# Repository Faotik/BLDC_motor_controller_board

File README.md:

# BLDC Motor Controller Board

A three-phase brushless DC (BLDC) motor controller built around an **STM32F405** microcontroller and a **DRV8305** gate driver. Designed in KiCad for a 12 V supply and 4 A motor current, with a 2x safety margin (8 A) in the power stage.

## Features

- **MCU:** STM32F405RGT6 with a 25 MHz crystal and SWD programming header
- **Motor control:** TIM1 complementary PWM outputs (CH1-3 and CH1N-3N), driver control over SPI, `EN_GATE`, `nFAULT` and `PWRGD` lines
- **Sensing:** shunt-based current sensing (4-wire Kelvin connections), phase voltage sensing (`VSEN_A/B/C`) and a Hall sensor connector
- **Power stage:** three half-bridges with wide power tracks and polygons for high current
- **Power supply:** 12 V input with polyfuse and TVS protection, LM2576 buck converter to 5 V, LM3940 LDO to 3.3 V
- **Wireless:** Bluetooth module

## Schematics

**MCU**

**Power supply**

## Repository layout

| Path | Contents |
|------|----------|
| `project.kicad_pro`, `project.kicad_sch`, `project.kicad_pcb` | KiCad project, top-level schematic and PCB |
| `STM32F405RGT`, `mcu`, `motor_driver`, `power_circuit`, `power_switches`, `bluetooth_module` (`.kicad_sch`) | Schematic sheets |
| `cubemx/` | STM32CubeMX pin and peripheral configuration |
| `Fabrication_files/` | Gerbers and drill files |
| `components/MyComponents.pretty` | Custom footprints |
| `project.csv`, `project-all-pos.csv` | BOM and component placement |

## Opening the project

Open `project.kicad_pro` in KiCad 10 or later.

## Status

Hardware design: schematics and PCB layout.

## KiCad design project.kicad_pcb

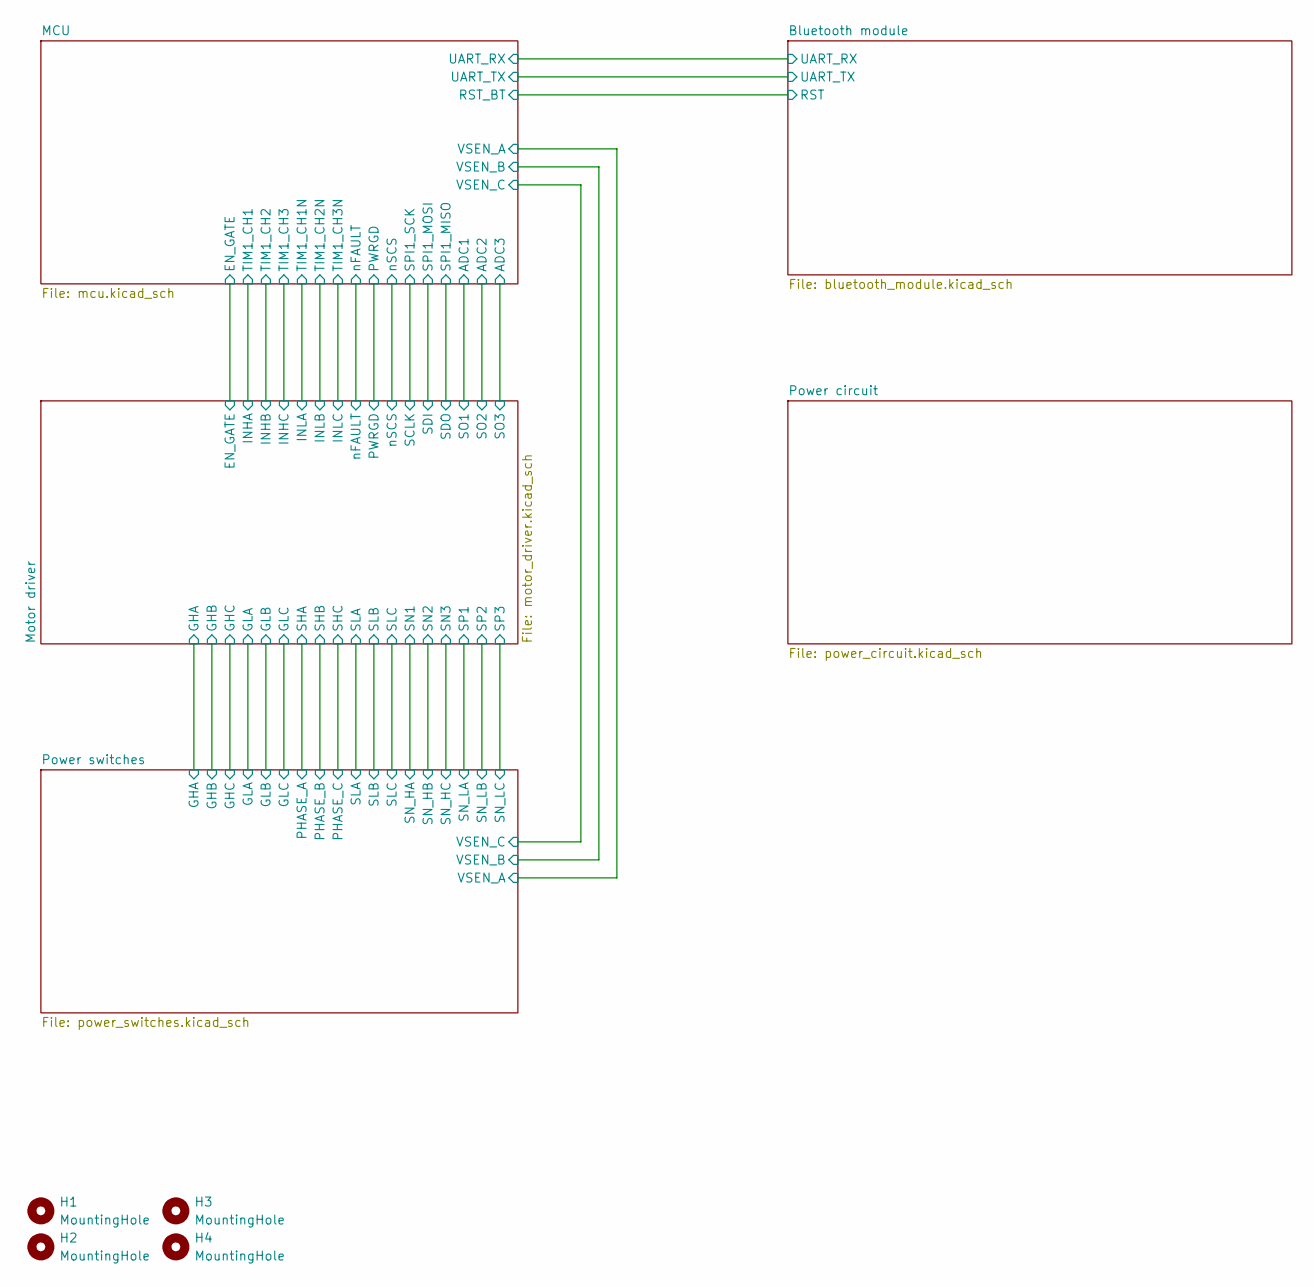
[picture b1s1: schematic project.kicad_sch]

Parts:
H1, H2, H3, H4: MountingHole; MountingHole_3mm_Pad

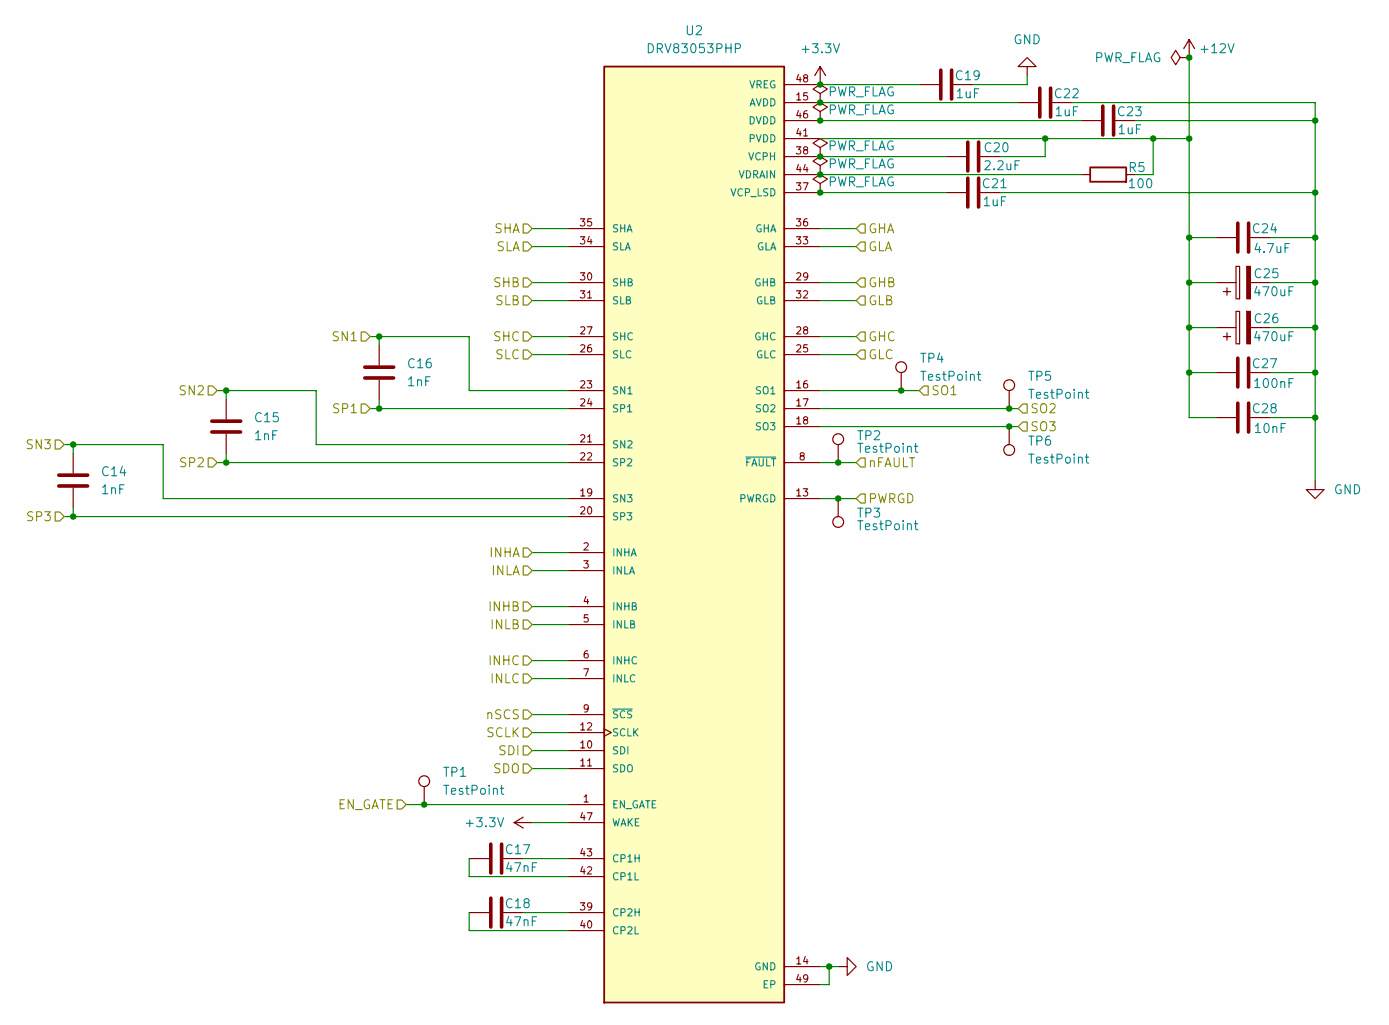
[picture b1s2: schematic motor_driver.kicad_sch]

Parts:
C14, C15, C16: 1nF; C_0402_1005Metric
C17, C18: 47nF; C_0603_1608Metric
C19, C21, C22, C23: 1uF; C_0603_1608Metric
C20: 2.2uF; C_0402_1005Metric
C24: 4.7uF; C_0805_2012Metric
C25, C26: 470uF; CAPPRD500W60D1000H1700
C27: 100nF; C_0402_1005Metric
C28: 10nF; C_0402_1005Metric
R5: 100; R_0603_1608Metric
TP1, TP2, TP3, TP4, TP5, TP6: TestPoint; TestPoint_Pad_D1.5mm
U2: DRV83053PHP; QFP50P900X900X120-49N; PARTREV B

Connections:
+3.3V: C19.1, U2.47 (WAKE), U2.48 (VREG); also elsewhere on the board
+12V: C20.1, C24.1, C25.1, C26.1, C27.1, C28.1, R5.2, U2.41 (PVDD); also elsewhere on the board
/MCU/ADC1: TP4.1 (1_1), U2.16 (SO1); also elsewhere on the board
/MCU/ADC2: TP5.1 (1_1), U2.17 (SO2); also elsewhere on the board
/MCU/ADC3: TP6.1 (1_1), U2.18 (SO3); also elsewhere on the board
/MCU/EN_GATE: TP1.1 (1_1), U2.1 (EN_GATE); also elsewhere on the board
/MCU/PWRGD: TP3.1 (1_1), U2.13 (PWRGD); also elsewhere on the board
/MCU/SPI1_MISO: U2.11 (SDO); also elsewhere on the board
/MCU/SPI1_MOSI: U2.10 (SDI); also elsewhere on the board
/MCU/SPI1_SCK: U2.12 (SCLK); also elsewhere on the board
/MCU/TIM1_CH1: U2.2 (INHA); also elsewhere on the board
/MCU/TIM1_CH1N: U2.3 (INLA); also elsewhere on the board
/MCU/TIM1_CH2: U2.4 (INHB); also elsewhere on the board
/MCU/TIM1_CH2N: U2.5 (INLB); also elsewhere on the board
/MCU/TIM1_CH3: U2.6 (INHC); also elsewhere on the board
/MCU/TIM1_CH3N: U2.7 (INLC); also elsewhere on the board
/MCU/nFAULT: TP2.1 (1_1), U2.8 (~FAULT); also elsewhere on the board
/MCU/nSCS: U2.9 (~SCS); also elsewhere on the board
/Motor driver/GHA: U2.36 (GHA); also elsewhere on the board
/Motor driver/GHB: U2.29 (GHB); also elsewhere on the board
/Motor driver/GHC: U2.28 (GHC); also elsewhere on the board
/Motor driver/GLA: U2.33 (GLA); also elsewhere on the board
/Motor driver/GLB: U2.32 (GLB); also elsewhere on the board
/Motor driver/GLC: U2.25 (GLC); also elsewhere on the board
/Motor driver/SLA: U2.34 (SLA); also elsewhere on the board
/Motor driver/SLB: U2.31 (SLB); also elsewhere on the board
/Motor driver/SLC: U2.26 (SLC); also elsewhere on the board
/Motor driver/SN1: C16.2, U2.23 (SN1); also elsewhere on the board
/Motor driver/SN2: C15.2, U2.21 (SN2); also elsewhere on the board
/Motor driver/SN3: C14.2, U2.19 (SN3); also elsewhere on the board
/Motor driver/SP1: C16.1, U2.24 (SP1); also elsewhere on the board
/Motor driver/SP2: C15.1, U2.22 (SP2); also elsewhere on the board
/Motor driver/SP3: C14.1, U2.20 (SP3); also elsewhere on the board
/Power switches/PHASE_A: U2.35 (SHA); also elsewhere on the board
/Power switches/PHASE_B: U2.30 (SHB); also elsewhere on the board
/Power switches/PHASE_C: U2.27 (SHC); also elsewhere on the board
GND: C19.2, C21.2, C22.2, C23.2, C24.2, C25.2, C26.2, C27.2, C28.2, U2.14 (GND), U2.45 (GND), U2.49 (EP), U2.49.1 (EP), U2.49.2 (EP), U2.49.3 (EP), U2.49.4 (EP), U2.49.5 (EP), U2.49.6 (EP), U2.49.7 (EP), U2.49.8 (EP), U2.49.9 (EP), U2.49.10 (EP), U2.49.11 (EP), U2.49.12 (EP), U2.49.13 (EP), U2.49.14 (EP), U2.49.15 (EP), U2.49.16 (EP), U2.49.17 (EP), U2.49.18 (EP), U2.49.19 (EP), U2.49.20 (EP), U2.49.21 (EP), U2.49.22 (EP), U2.49.23 (EP), U2.49.24 (EP), U2.49.25 (EP); also elsewhere on the board
unnamed: C22.1, U2.15 (AVDD)
unnamed: C17.2, U2.43 (CP1H)
unnamed: C17.1, U2.42 (CP1L)
unnamed: C18.2, U2.39 (CP2H)
unnamed: C18.1, U2.40 (CP2L)
unnamed: C23.1, U2.46 (DVDD)
unnamed: C20.2, U2.38 (VCPH)
unnamed: C21.1, U2.37 (VCP_LSD)
unnamed: R5.1, U2.44 (VDRAIN)

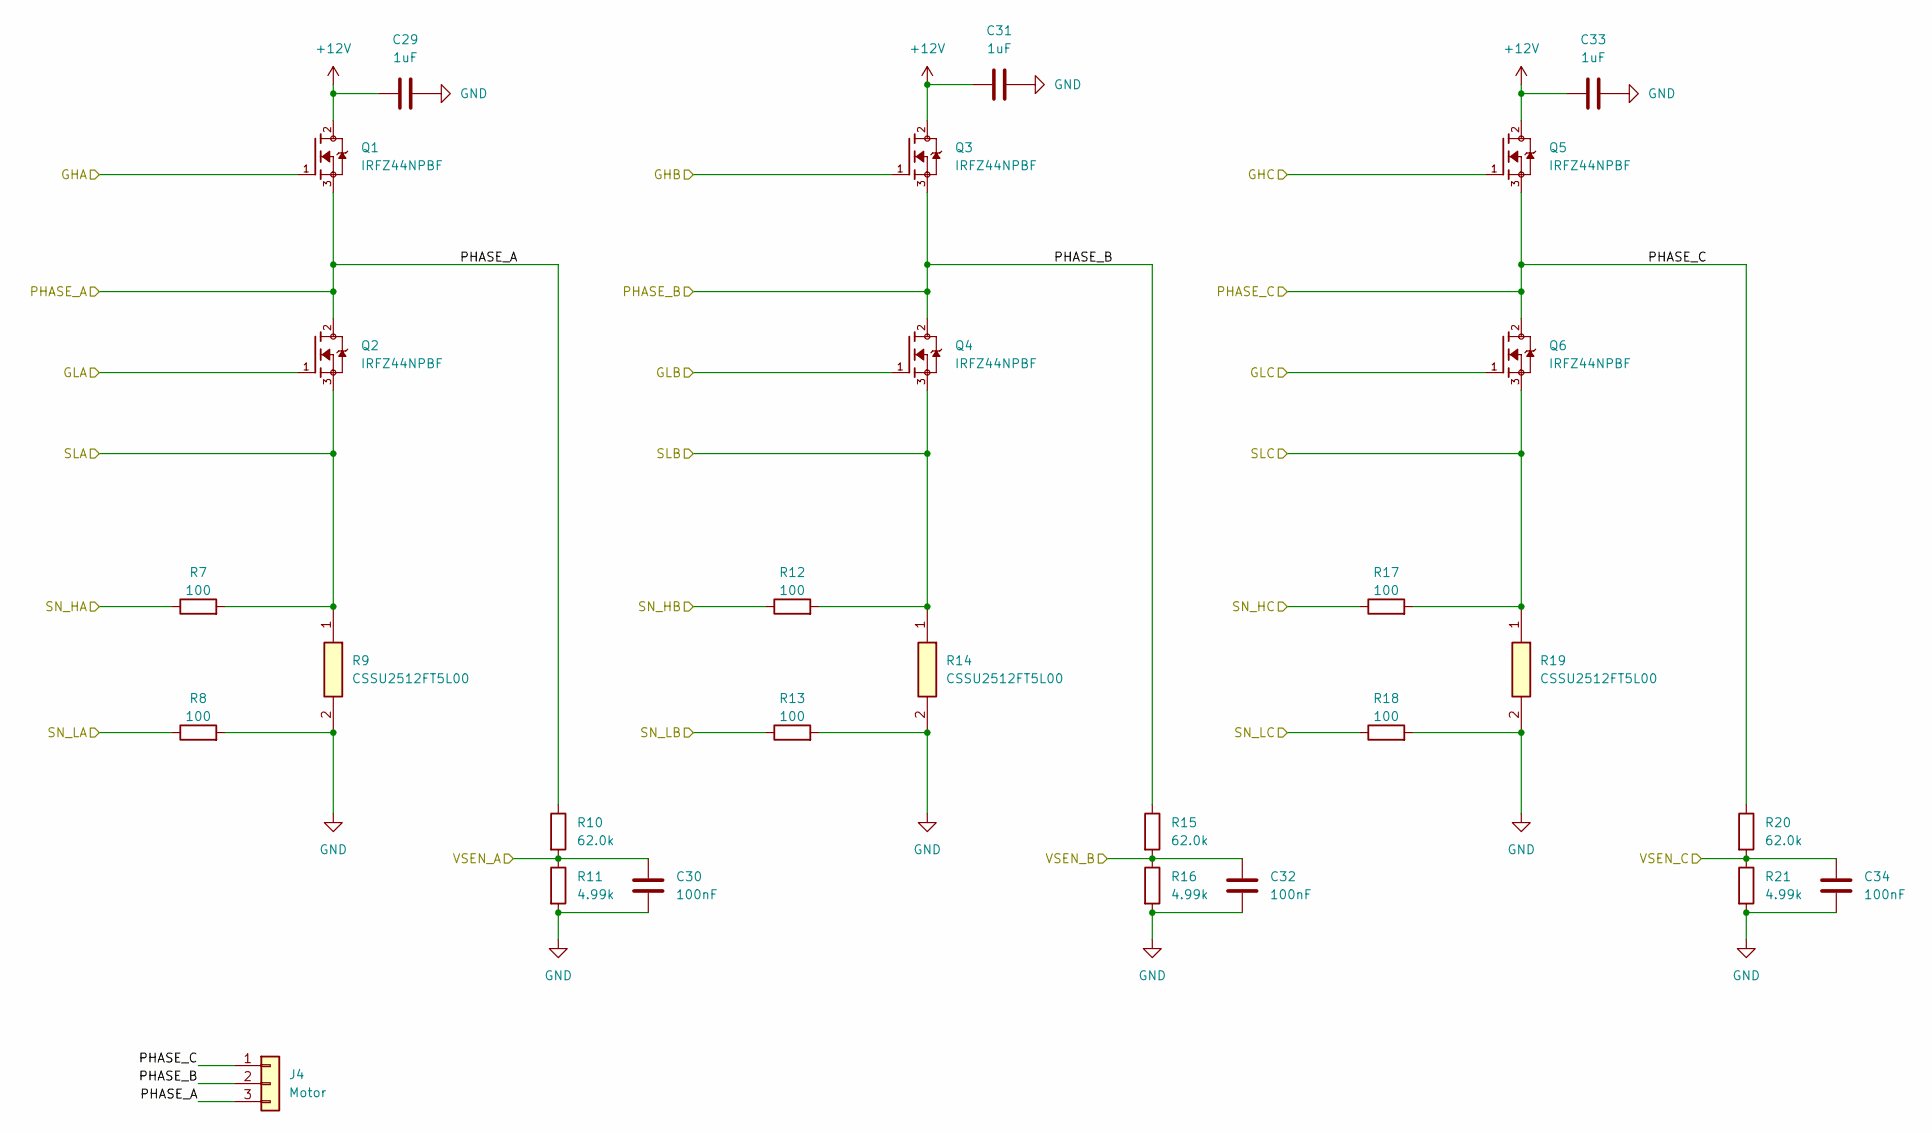
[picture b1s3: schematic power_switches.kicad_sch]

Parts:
C29, C31, C33: 1uF; C_0603_1608Metric
C30, C32, C34: 100nF; C_0402_1005Metric
J4: Motor; TerminalBlock_Phoenix_MKDS-1,5-3-5.08_1x03_P5.08mm_Horizont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
Q1, Q2, Q3, Q4, Q5, Q6: IRFZ44NPBF; TO254P1016X419X2286-3; PARTREV 09/21/10
R7, R8, R12, R13, R17, R18: 100; R_0603_1608Metric
R9, R14, R19: CSSU2512FT5L00; RESC6430X100N; Manufacturer_Part_Number CSSU2512FT5L00
R10, R15, R20: 62.0k; R_0603_1608Metric
R11, R16, R21: 4.99k; R_0603_1608Metric

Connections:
+12V: C29.1, C31.1, C33.1, Q1.2, Q3.2, Q5.2; also elsewhere on the board
/MCU/VSEN_A: C30.1, R10.2, R11.1; also elsewhere on the board
/MCU/VSEN_B: C32.1, R15.2, R16.1; also elsewhere on the board
/MCU/VSEN_C: C34.1, R20.2, R21.1; also elsewhere on the board
/Motor driver/GHA: Q1.1; also elsewhere on the board
/Motor driver/GHB: Q3.1; also elsewhere on the board
/Motor driver/GHC: Q5.1; also elsewhere on the board
/Motor driver/GLA: Q2.1; also elsewhere on the board
/Motor driver/GLB: Q4.1; also elsewhere on the board
/Motor driver/GLC: Q6.1; also elsewhere on the board
/Motor driver/SLA: Q2.3, R7.2, R9.1; also elsewhere on the board
/Motor driver/SLB: Q4.3, R12.2, R14.1; also elsewhere on the board
/Motor driver/SLC: Q6.3, R17.2, R19.1; also elsewhere on the board
/Motor driver/SN1: R7.1; also elsewhere on the board
/Motor driver/SN2: R12.1; also elsewhere on the board
/Motor driver/SN3: R17.1; also elsewhere on the board
/Motor driver/SP1: R8.1; also elsewhere on the board
/Motor driver/SP2: R13.1; also elsewhere on the board
/Motor driver/SP3: R18.1; also elsewhere on the board
/Power switches/PHASE_A: J4.3, Q1.3, Q2.2, R10.1; also elsewhere on the board
/Power switches/PHASE_B: J4.2, Q3.3, Q4.2, R15.1; also elsewhere on the board
/Power switches/PHASE_C: J4.1, Q5.3, Q6.2, R20.1; also elsewhere on the board
GND: C29.2, C30.2, C31.2, C32.2, C33.2, C34.2, R8.2, R9.2, R11.2, R13.2, R14.2, R16.2, R18.2, R19.2, R21.2; also elsewhere on the board

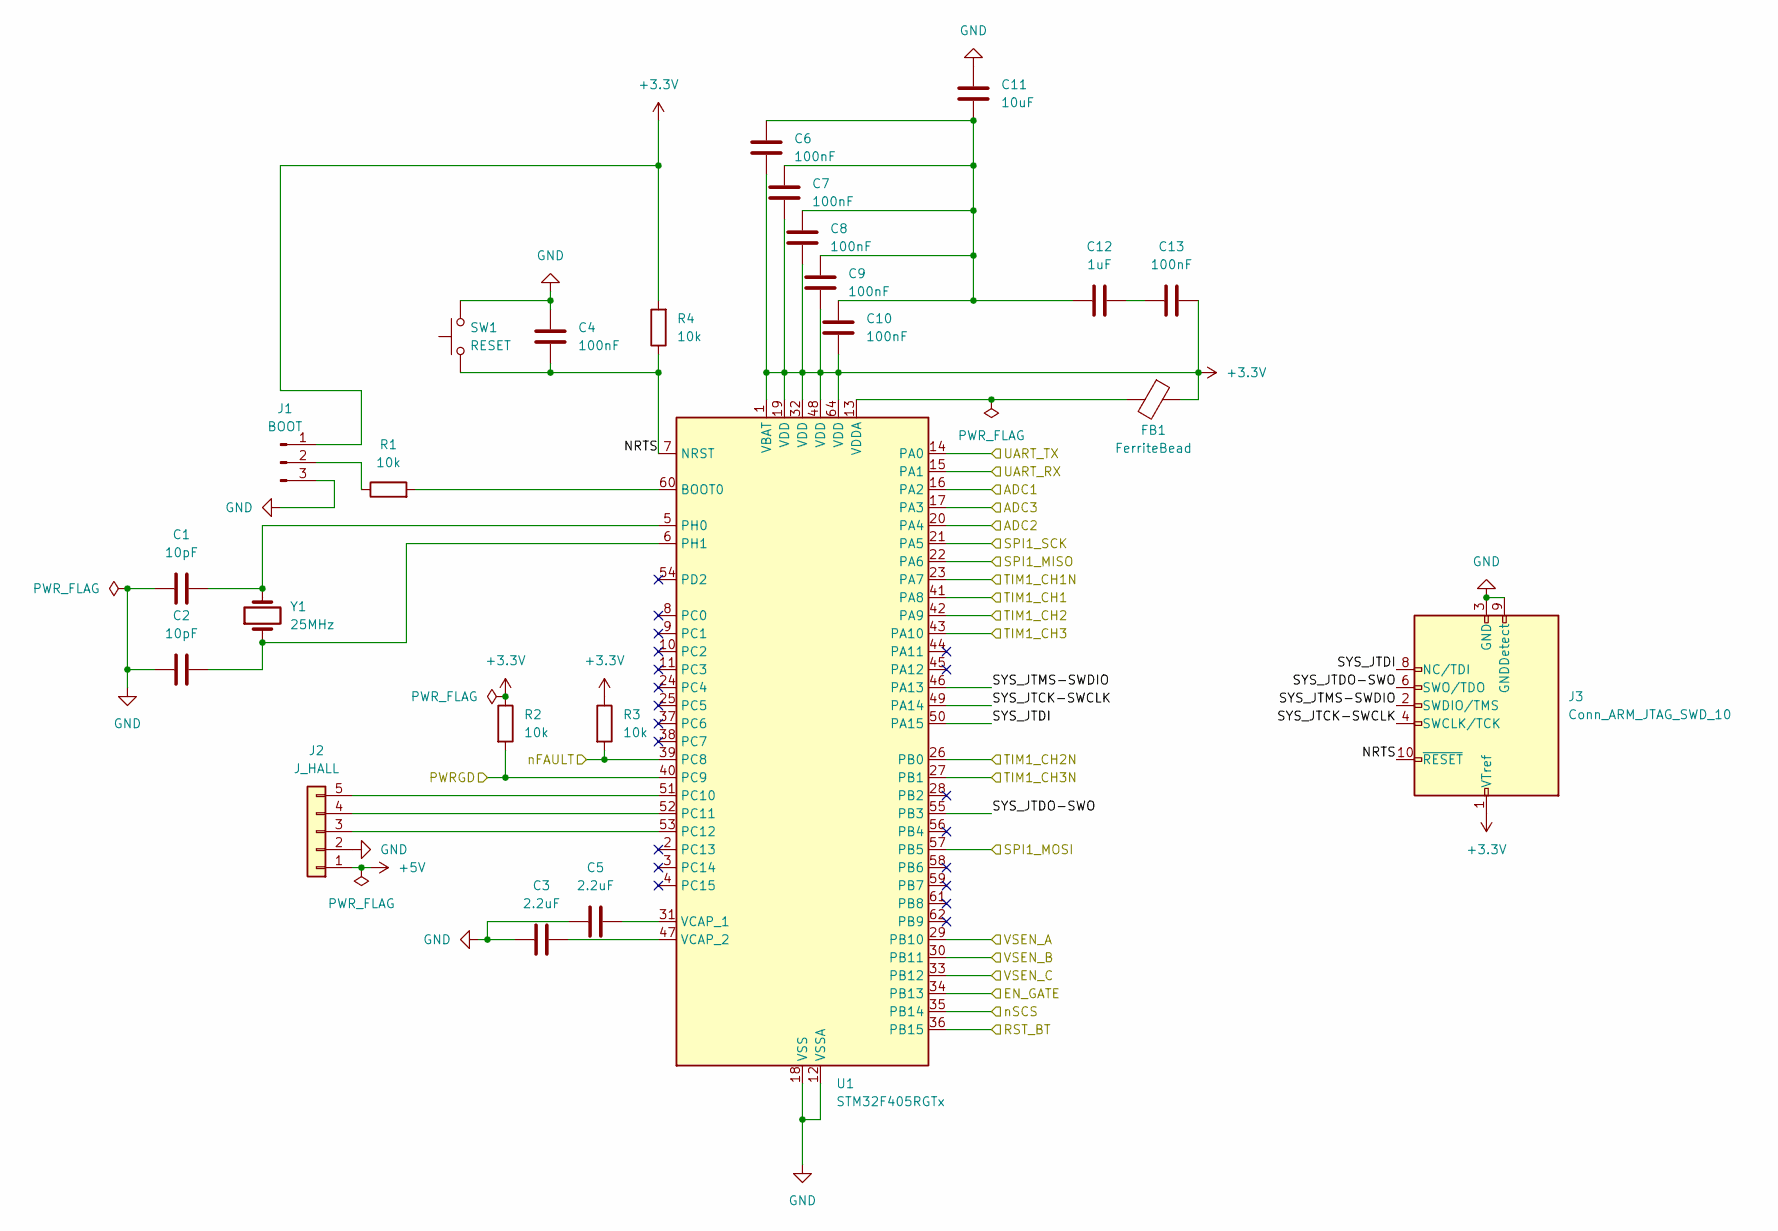
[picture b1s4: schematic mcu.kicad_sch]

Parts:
C1, C2: 10pF; C_0603_1608Metric
C3, C5: 2.2uF; C_0402_1005Metric
C4, C6, C7, C8, C9, C10, C13: 100nF; C_0201_0603Metric
C11: 10uF; C_0805_2012Metric
C12: 1uF; C_0201_0603Metric
FB1: FerriteBead; L_0402_1005Metric
J1: BOOT; PinHeader_1x03_P2.54mm_Vertical
J2: J_HALL; JST_PH_B5B-PH-K_1x05_P2.00mm_Vertical
J3: Conn_ARM_JTAG_SWD_10; PinHeader_2x05_P1.27mm_Vertical_SMD
R1, R2, R3, R4: 10k; R_0603_1608Metric
SW1: RESET; SW_Push_1P1T_NO_CK_KSC6xxJ
U1: STM32F405RGTx; LQFP-64_10x10mm_P0.5mm
Y1: 25MHz; Crystal_SMD_Abracon_ABM7-2Pin_6.0x3.5mm

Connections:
+3.3V: C6.1, C7.1, C8.1, C9.1, C10.1, C13.1, FB1.1, J1.1, J3.1 (VTref), R2.1, R3.1, R4.2, U1.1 (VBAT), U1.19 (VDD), U1.32 (VDD), U1.48 (VDD), U1.64 (VDD); also elsewhere on the board
+5V: J2.1; also elsewhere on the board
/Bluetooth module/RST: U1.36 (PB15); also elsewhere on the board
/Bluetooth module/UART_RX: U1.15 (PA1); also elsewhere on the board
/Bluetooth module/UART_TX: U1.14 (PA0); also elsewhere on the board
/MCU/ADC1: U1.16 (PA2); also elsewhere on the board
/MCU/ADC2: U1.20 (PA4); also elsewhere on the board
/MCU/ADC3: U1.17 (PA3); also elsewhere on the board
/MCU/EN_GATE: U1.34 (PB13); also elsewhere on the board
/MCU/NRTS: C4.2, J3.10 (~RESET), R4.1, SW1.1, U1.7 (NRST)
/MCU/PWRGD: R2.2, U1.40 (PC9); also elsewhere on the board
/MCU/SPI1_MISO: U1.22 (PA6); also elsewhere on the board
/MCU/SPI1_MOSI: U1.57 (PB5); also elsewhere on the board
/MCU/SPI1_SCK: U1.21 (PA5); also elsewhere on the board
/MCU/SYS_JTCK-SWCLK: J3.4 (SWCLK/TCK), U1.49 (PA14)
/MCU/SYS_JTDI: J3.8 (NC/TDI), U1.50 (PA15)
/MCU/SYS_JTDO-SWO: J3.6 (SWO/TDO), U1.55 (PB3)
/MCU/SYS_JTMS-SWDIO: J3.2 (SWDIO/TMS), U1.46 (PA13)
/MCU/TIM1_CH1: U1.41 (PA8); also elsewhere on the board
/MCU/TIM1_CH1N: U1.23 (PA7); also elsewhere on the board
/MCU/TIM1_CH2: U1.42 (PA9); also elsewhere on the board
/MCU/TIM1_CH2N: U1.26 (PB0); also elsewhere on the board
/MCU/TIM1_CH3: U1.43 (PA10); also elsewhere on the board
/MCU/TIM1_CH3N: U1.27 (PB1); also elsewhere on the board
/MCU/VSEN_A: U1.29 (PB10); also elsewhere on the board
/MCU/VSEN_B: U1.30 (PB11); also elsewhere on the board
/MCU/VSEN_C: U1.33 (PB12); also elsewhere on the board
/MCU/nFAULT: R3.2, U1.39 (PC8); also elsewhere on the board
/MCU/nSCS: U1.35 (PB14); also elsewhere on the board
GND: C1.2, C2.2, C3.1, C4.1, C5.1, C11.1, J1.3, J2.2, J3.3 (GND), J3.5 (GND), J3.9 (GNDDetect), SW1.2, U1.12 (VSSA), U1.18 (VSS), U1.63 (VSS); also elsewhere on the board
unnamed: C6.2, C7.2, C8.2, C9.2, C10.2, C11.2, C12.2
unnamed: C12.1, C13.2
unnamed: J1.2, R1.1
unnamed: J2.3, U1.53 (PC12)
unnamed: J2.4, U1.52 (PC11)
unnamed: J2.5, U1.51 (PC10)
unnamed: R1.2, U1.60 (BOOT0)
unnamed: C1.1, U1.5 (PH0), Y1.2
unnamed: C2.1, U1.6 (PH1), Y1.1
unnamed: C5.2, U1.31 (VCAP_1)
unnamed: C3.2, U1.47 (VCAP_2)
unnamed: FB1.2, U1.13 (VDDA)

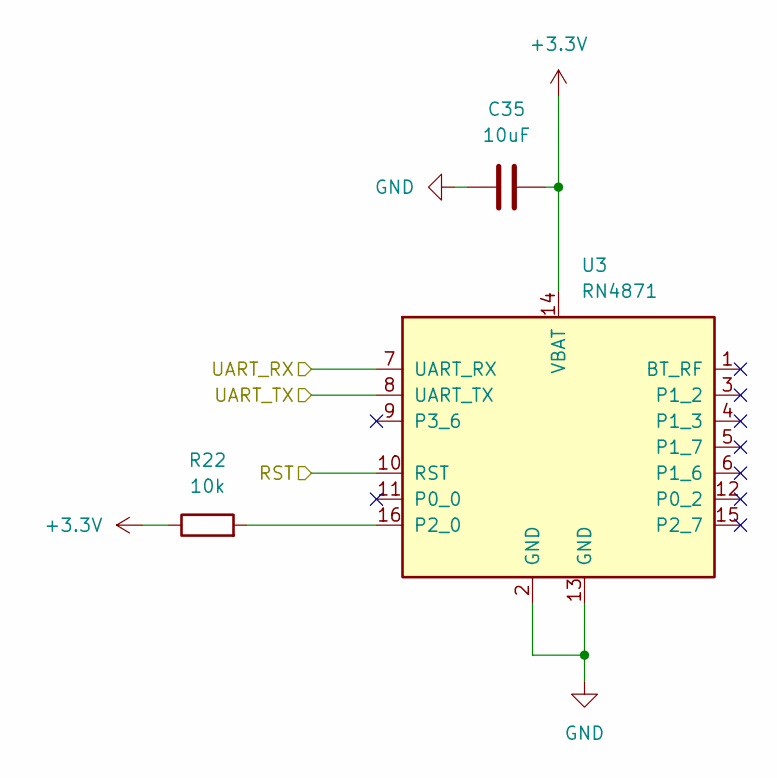
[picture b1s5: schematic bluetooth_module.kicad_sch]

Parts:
C35: 10uF; C_0805_2012Metric
R22: 10k; R_0603_1608Metric
U3: RN4871; Microchip_RN4871

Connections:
+3.3V: C35.1, R22.1, U3.14 (VBAT); also elsewhere on the board
/Bluetooth module/RST: U3.10 (RST); also elsewhere on the board
/Bluetooth module/UART_RX: U3.7 (UART_RX); also elsewhere on the board
/Bluetooth module/UART_TX: U3.8 (UART_TX); also elsewhere on the board
GND: C35.2, U3.2 (GND), U3.13 (GND); also elsewhere on the board
unnamed: R22.2, U3.16 (P2_0)

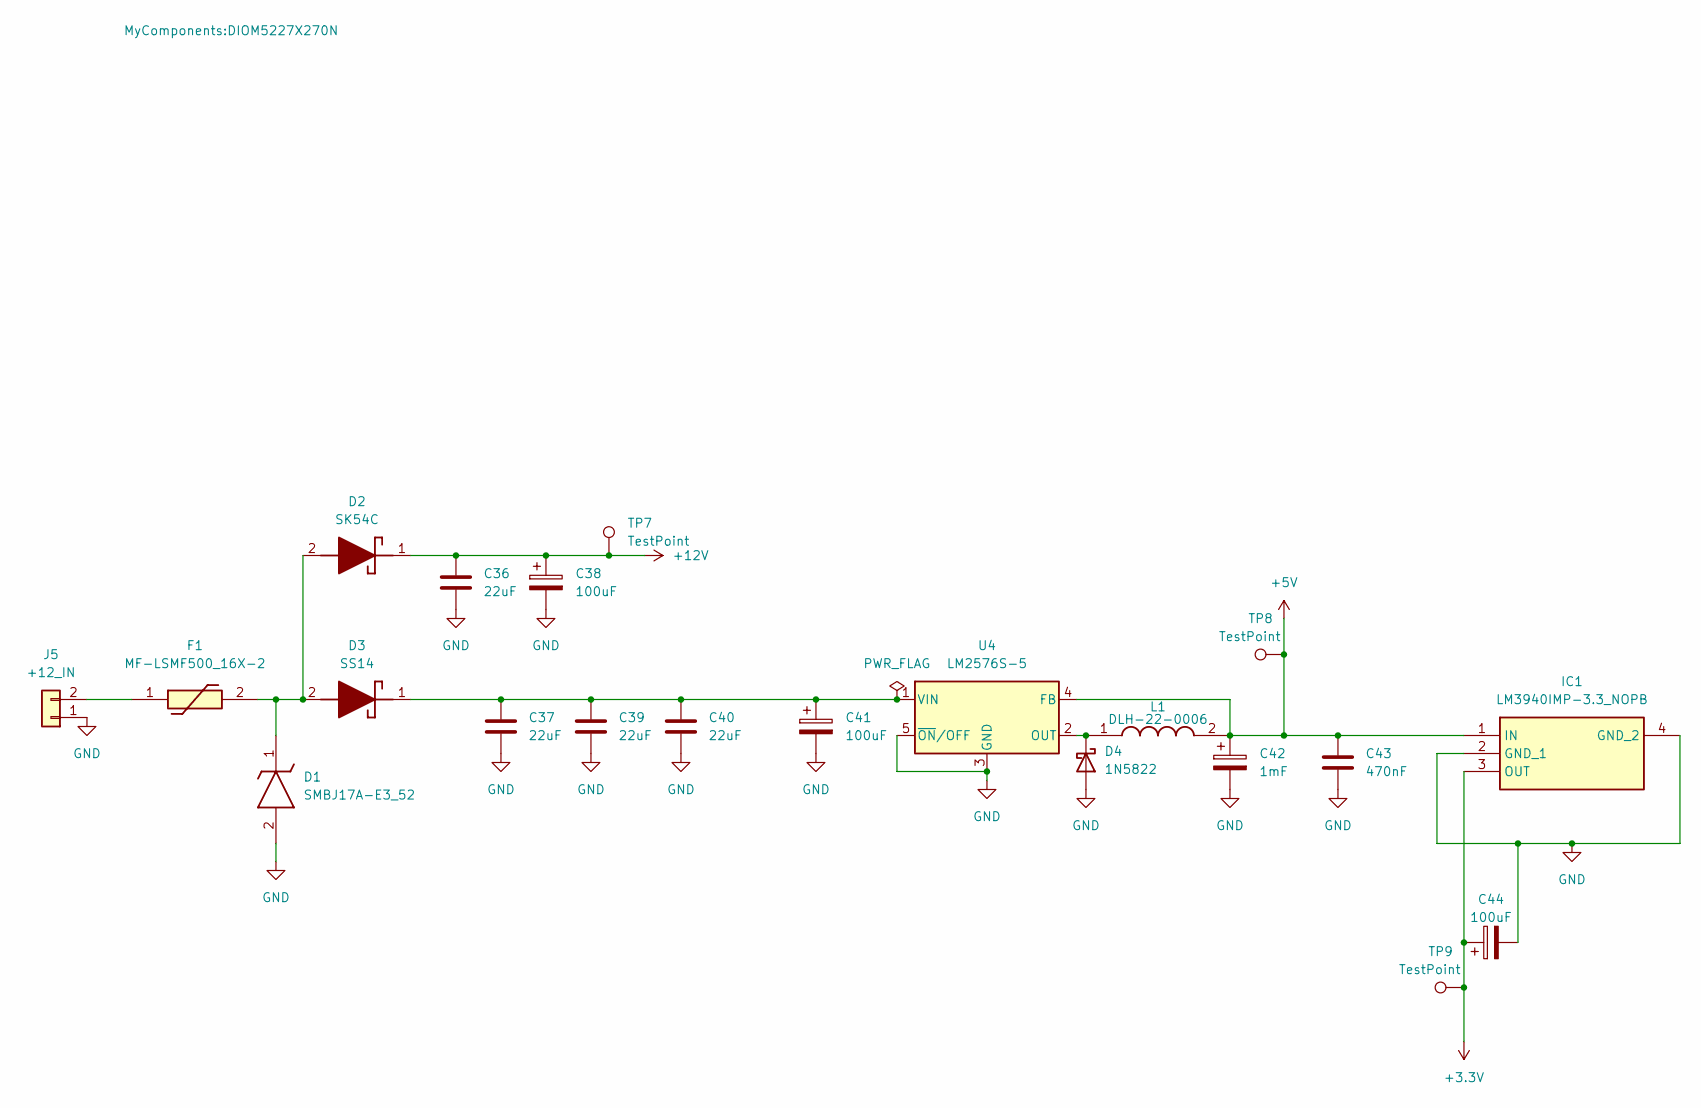
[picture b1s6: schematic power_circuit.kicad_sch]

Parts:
C36, C37, C39, C40: 22uF; C_0805_2012Metric
C38, C41, C44: 100uF; CAPPRD200W50D500H1250
C42: 1mF; CAPPRD500W60D1000H2200
C43: 470nF; C_0603_1608Metric
D1: SMBJ17A-E3_52; DIOM5436X244N; Manufacturer_Part_Number SMBJ17A-E3/52
D2: SK54C; DIOM7959X262N; Manufacturer_Part_Number SK54C
D3: SS14; DIOM5227X270N; Manufacturer_Part_Number SS14
D4: 1N5822; D_DO-201AD_P15.24mm_Horizontal
F1: MF-LSMF500_16X-2; MFLSMF50016X2; Manufacturer_Part_Number MF-LSMF500/16X-2
IC1: LM3940IMP-3.3_NOPB; SOT230P700X180-4N; Manufacturer_Part_Number LM3940IMP-3.3/NOPB
J5: +12_IN; AMASS_XT30PW-M_1x02_P2.50mm_Horizontal
L1: DLH-22-0006; DLH220006; Manufacturer_Part_Number DLH-22-0006; Mouser Part Number 693-DLH-22-0006
TP7, TP8, TP9: TestPoint; TestPoint_THTPad_D1.5mm_Drill0.7mm
U4: LM2576S-5; TO-263-5_TabPin3

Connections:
+3.3V: C44.1, IC1.3 (OUT), TP9.1 (1_1); also elsewhere on the board
+5V: C42.1, C43.1, IC1.1 (IN), L1.2 (2_4), TP8.1 (1_1), U4.4 (FB); also elsewhere on the board
+12V: C36.1, C38.1, D2.1 (K), TP7.1 (1_1); also elsewhere on the board
GND: C36.2, C37.2, C38.2, C39.2, C40.2, C41.2, C42.2, C43.2, C44.2, D1.2 (A), D4.2 (A), IC1.2 (GND_1), IC1.4 (GND_2), J5.1, U4.3 (GND), U4.5 (~ON/OFF); also elsewhere on the board
unnamed: D1.1 (K), D2.2 (A), D3.2 (A), F1.2
unnamed: C37.1, C39.1, C40.1, C41.1, D3.1 (K), U4.1 (VIN)
unnamed: D4.1 (K), L1.1 (1_2), U4.2 (OUT)
unnamed: F1.1, J5.2

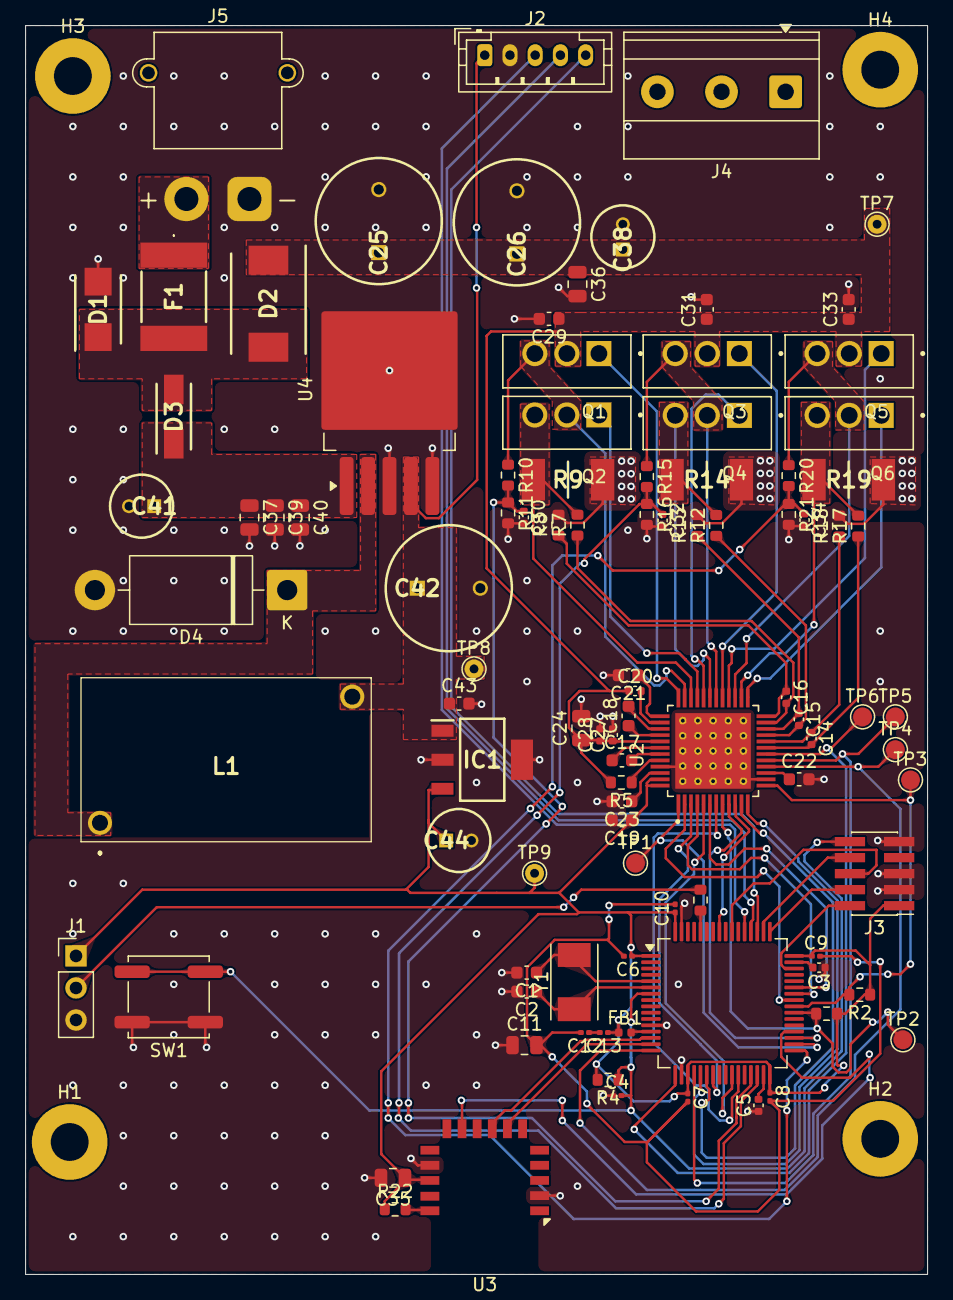
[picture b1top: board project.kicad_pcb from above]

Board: 4 copper layers, 71.5 x 99.0 mm, 103 parts (0 on the bottom side), 75 nets.

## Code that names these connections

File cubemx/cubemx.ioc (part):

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Mcu.Name=STM32F405RGTx
Mcu.Package=LQFP64
Mcu.UserName=STM32F405RGTx
PA0-WKUP.Mode=Asynchronous
PA0-WKUP.Signal=UART4_TX
PA1.Mode=Asynchronous
PA1.Signal=UART4_RX
PA10.Signal=S_TIM1_CH3
PA13.Mode=JTAG_4_pins
PA13.Signal=SYS_JTMS-SWDIO
PA14.Mode=JTAG_4_pins
PA14.Signal=SYS_JTCK-SWCLK
PA15.Mode=JTAG_4_pins
PA15.Signal=SYS_JTDI
PA2.Signal=ADCx_IN2
PA3.Signal=ADCx_IN3
PA4.Signal=ADCx_IN4
PA5.Mode=Full_Duplex_Master
PA5.Signal=SPI1_SCK
PA6.Mode=Full_Duplex_Master
PA6.Signal=SPI1_MISO
PA7.Mode=Output Compare1 CH1 CH1N
PA7.Signal=TIM1_CH1N
PA8.Signal=S_TIM1_CH1
PA9.Signal=S_TIM1_CH2
PB0.Mode=Output Compare2 CH2 CH2N
PB0.Signal=TIM1_CH2N
PB1.Mode=Output Compare3 CH3 CH3N
PB1.Signal=TIM1_CH3N
PB10.Signal=GPIO_Analog
PB11.Signal=GPIO_Analog
PB12.Signal=GPIO_Analog
PB13.Signal=GPIO_Input
PB14.Signal=GPIO_Output
PB15.Signal=GPIO_Output
PB3.Mode=JTAG_4_pins
PB3.Signal=SYS_JTDO-SWO
PB5.Mode=Full_Duplex_Master
PB5.Signal=SPI1_MOSI
PC10.Signal=GPIO_Input
PC11.Signal=GPIO_Input
PC12.Signal=GPIO_Input
PC8.Signal=GPIO_Input
PC9.Signal=GPIO_Input
PH0-OSC_IN.Mode=HSE-External-Oscillator
PH0-OSC_IN.Signal=RCC_OSC_IN
PH1-OSC_OUT.Mode=HSE-External-Oscillator
PH1-OSC_OUT.Signal=RCC_OSC_OUT
RCC.HSE_VALUE=25000000
RCC.SYSCLKFreq_VALUE=16000000
board=custom
